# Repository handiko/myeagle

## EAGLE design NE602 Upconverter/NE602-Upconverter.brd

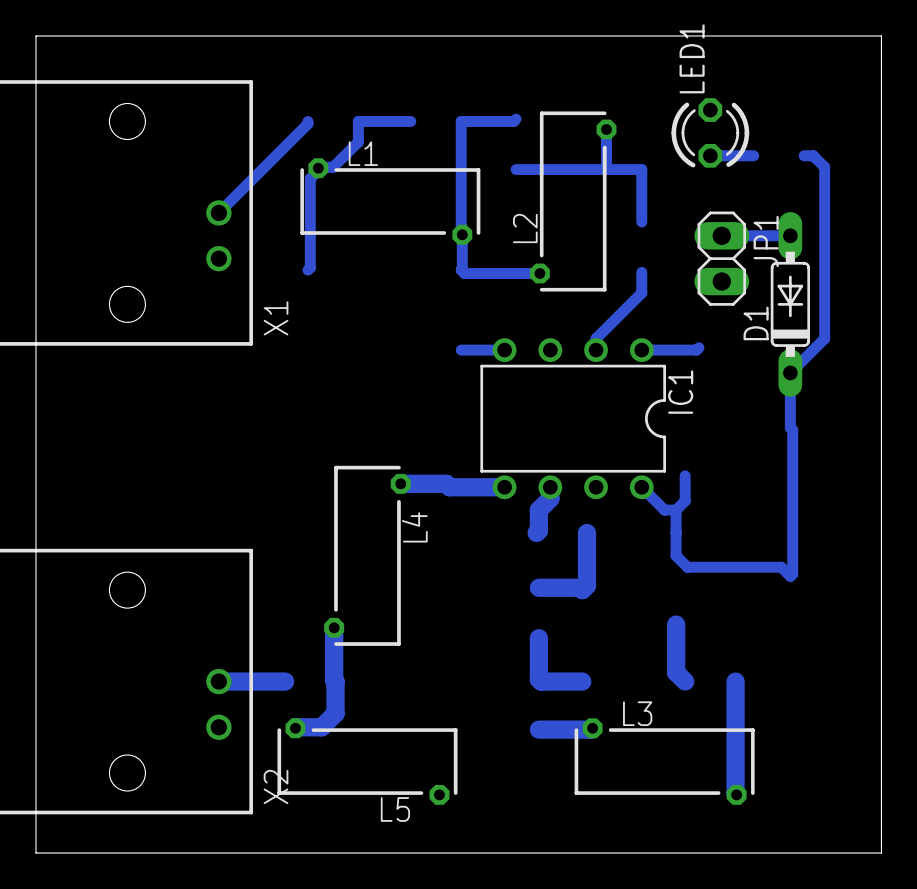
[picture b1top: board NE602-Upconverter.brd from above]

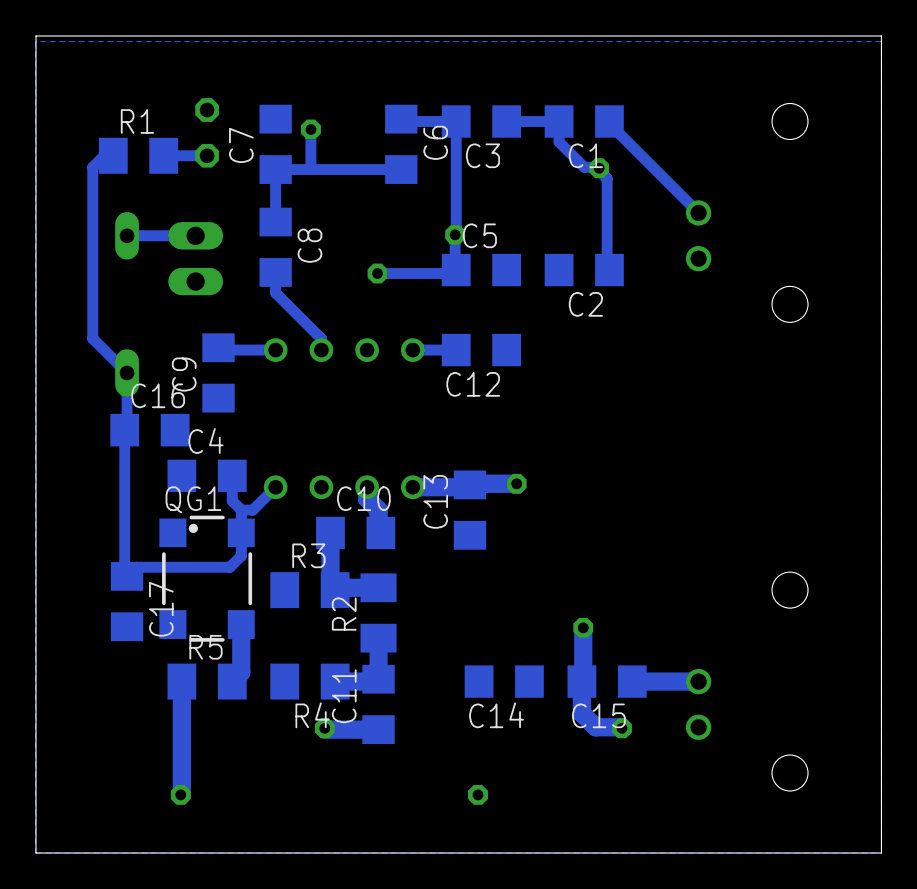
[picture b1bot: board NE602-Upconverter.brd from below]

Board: 2 copper layers, 47.0 x 45.4 mm, 34 parts (23 on the bottom side), 21 nets.

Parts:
C1, C2, C3, C4, C5, C6, C7, C8, C9, C10, C11, C12, C13, C14, C15, C16, C17: C1206
D1: 1N4148DO35-7; DO35-7
IC1: SA612AN; DIL08
JP1: 1X02
L1, L2, L3, L4, L5: Z28/7
LED1: LED3MM
QG1: SM77H
R1, R2, R3, R4, R5: M1206
X1, X2: 1-227161-0; AMP_227161

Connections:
+5V: C4.2, C16.1, C17.1, D1.C, IC1.8, QG1.4, R1.1
GND: C2.2, C4.1, C5.2, C7.2, C9.1, C12.1, C13.1, C14.1, C16.2, C17.2, IC1.3, JP1.2, LED1.K, QG1.2, R3.1, R4.2, X1.2, X2.2
unnamed: C1.2, C2.1, C3.1, L1.2
unnamed: C3.2, C5.1, C6.1, L1.1, L2.2
unnamed: C6.2, C7.1, C8.1, L2.1
unnamed: C8.2, IC1.2
unnamed: C9.2, IC1.1
unnamed: C10.2, IC1.6
unnamed: C14.2, L5.2
unnamed: C13.2, IC1.5, L4.2
unnamed: C15.2, L4.1, L5.1
unnamed: C12.2, IC1.4
unnamed: C11.2, R2.1, R4.1
unnamed: C10.1, R2.2, R3.2
unnamed: C11.1, L3.2
unnamed: LED1.A, R1.2
unnamed: L3.1, R5.1
unnamed: QG1.3, R5.2
unnamed: C1.1, X1.1
unnamed: C15.1, X2.1
unnamed: D1.A, JP1.1

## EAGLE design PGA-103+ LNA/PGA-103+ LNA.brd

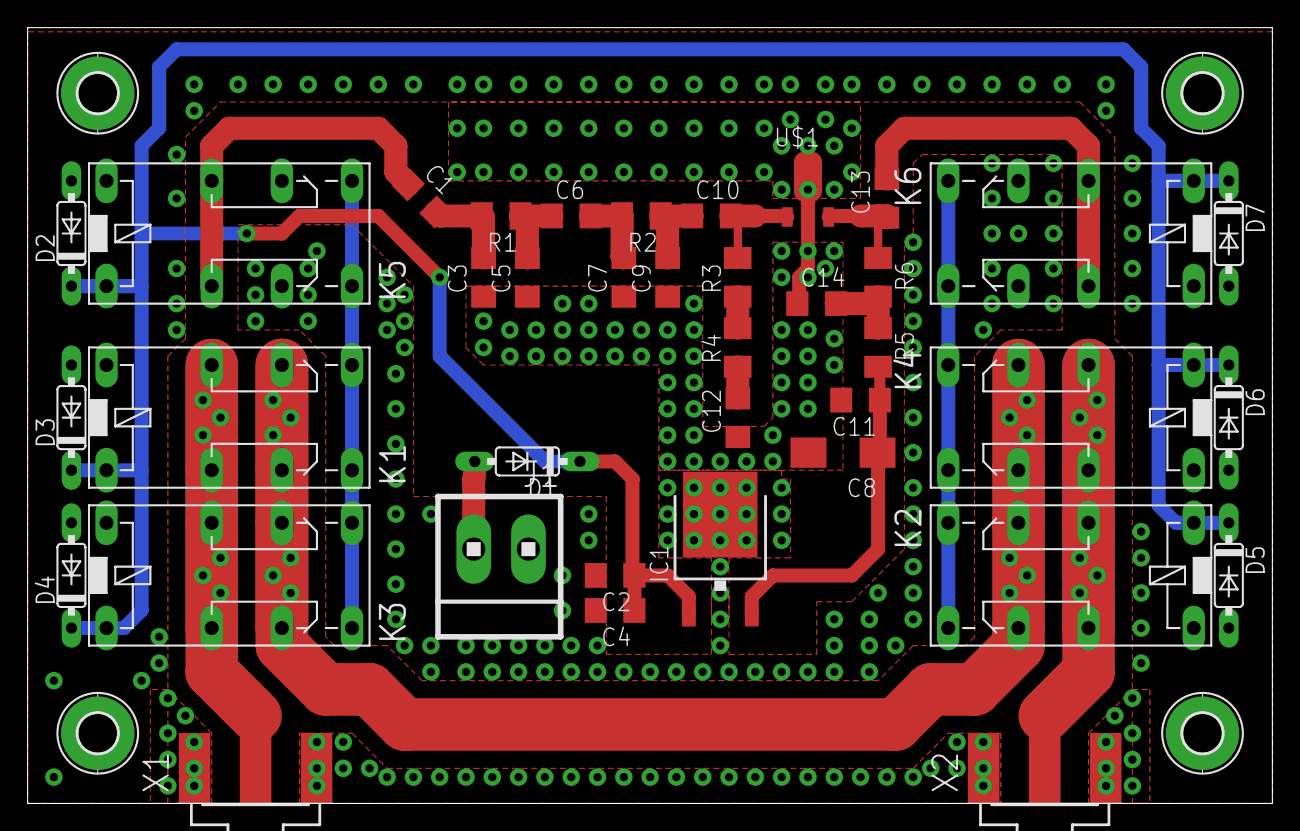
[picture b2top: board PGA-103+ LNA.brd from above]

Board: 2 copper layers, 90.2 x 56.2 mm, 42 parts (0 on the bottom side), 20 nets.

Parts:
C1, C6, C10, C13: 10n; C1206
C2, C4, C11, C14: 1n; C1206
C3, C5, C7, C9, C12: 330p; C1206
C8: 10u; CT6032
D1, D2, D3, D4, D5, D6, D7: 1N4xxx; DO35-7
H1, H2, H3, H4: MOUNT-PAD; 2,8-PAD
IC1: 7805DT; TO252
J1: 1X2MTA
K1, K2, K3, K4, K5, K6: 351
R1, R2, R3, R6: 1u; M1206
R4: 150; M1206
R5: 22; M1206
U$1: PGA-103; DF782
X1, X2: SMA; J502-ND-142-0701-851/861

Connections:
ANT: K1.P1, K1.P2, K3.P1, K3.P2, X1.1
GND: C2.2, C3.1, C4.2, C5.1, C7.1, C8.-, C9.1, C11.2, C12.1, C14.1, D2.A, D3.A, D4.A, D5.A, D6.A, D7.A, H1.B2,8, H2.B2,8, H3.B2,8, H4.B2,8, IC1.3, J1.2, K1.16, K2.16, K3.16, K4.16, K5.16, K5.O1, K5.O2, K6.16, K6.O1, K6.O2, U$1.GND-1, U$1.GND-2, X1.G@1, X1.G@2, X1.G@3, X1.G@4, X2.G@1, X2.G@2, X2.G@3, X2.G@4
LNA_IN: C1.1, K5.P1, K5.P2
LNA_OUT: C13.2, K6.P1, K6.P2
unnamed: C10.2, R3.2, U$1.RF-IN
unnamed: C13.1, R6.1, U$1.RF-OUT
unnamed: C8.+, C11.1, IC1.2, R5.2
unnamed: D1.A, J1.1
unnamed: C9.2, C10.1, R2.1
unnamed: C14.2, R5.1, R6.2
unnamed: R3.1, R4.2
unnamed: C12.2, R4.1
unnamed: C6.2, C7.2, R2.2
unnamed: C5.2, C6.1, R1.1
unnamed: C1.2, C3.2, R1.2
unnamed: K1.S1, K1.S2, K3.S1, K3.S2, K5.S1, K5.S2
unnamed: K2.S1, K2.S2, K4.S1, K4.S2, K6.S1, K6.S2
RF_BYPASS: K1.O1, K1.O2, K2.O1, K2.O2, K3.O1, K3.O2, K4.O1, K4.O2
TRX: K2.P1, K2.P2, K4.P1, K4.P2, X2.1
VCC: C2.1, C4.1, D1.C, D2.C, D3.C, D4.C, D5.C, D6.C, D7.C, IC1.1, K1.1, K2.1, K3.1, K4.1, K5.1, K6.1

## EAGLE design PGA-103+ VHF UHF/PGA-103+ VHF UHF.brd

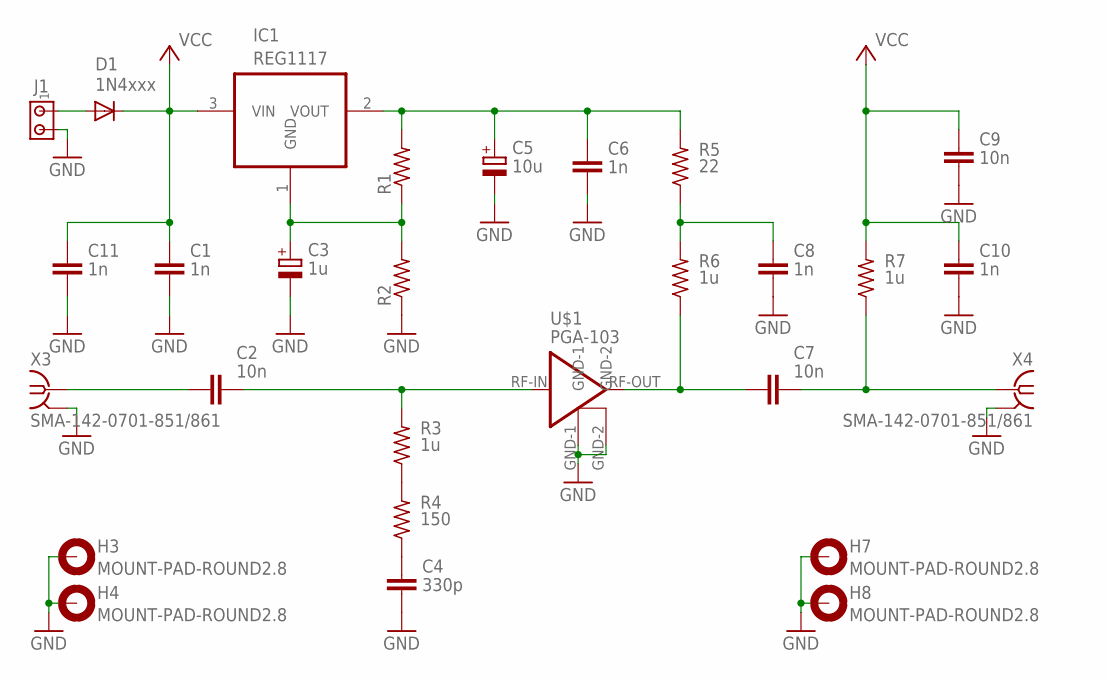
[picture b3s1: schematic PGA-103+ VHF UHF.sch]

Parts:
C1, C6, C8, C10, C11: 1n; C1206
C2, C7, C9: 10n; C1206
C3: 1u; CT6032
C4: 330p; C1206
C5: 10u; CT6032
D1: 1N4xxx; DO35-7
H3, H4, H7, H8: MOUNT-PAD-ROUND2.8; 2,8-PAD
IC1: REG1117; SOT223
J1: MTA02-156; 1X2MTA
R1, R2: R-US_M1206; M1206
R3, R6, R7: 1u; M1206
R4: 150; M1206
R5: 22; M1206
U$1: PGA-103; DF782
X3, X4: SMA-142-0701-851/861; J502-ND-142-0701-851/861

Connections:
GND: C1.2, C3.-, C4.1, C5.-, C6.2, C8.1, C9.1, C10.1, C11.2, H3.B2,8, H4.B2,8, H7.B2,8, H8.B2,8, J1.2, R2.1, U$1.GND-1, U$1.GND-2, X3.G@1 (2), X3.G@2 (2), X3.G@3 (2), X3.G@4 (2), X4.G@1 (2), X4.G@2 (2), X4.G@3 (2), X4.G@4 (2)
unnamed: C2.2, R3.2, U$1.RF-IN
unnamed: C2.1, X3.1
unnamed: C7.1, R6.1, U$1.RF-OUT
unnamed: C7.2, R7.1, X4.1
unnamed: C5.+, C6.1, IC1.2 (VOUT), R1.2, R5.2
unnamed: C3.+, IC1.1 (GND), R1.1, R2.2
unnamed: D1.A, J1.1
unnamed: C8.2, R5.1, R6.2
unnamed: R3.1, R4.2
unnamed: C4.2, R4.1
VCC: C1.1, C9.2, C10.2, C11.1, D1.C, IC1.3 (VIN), R7.2

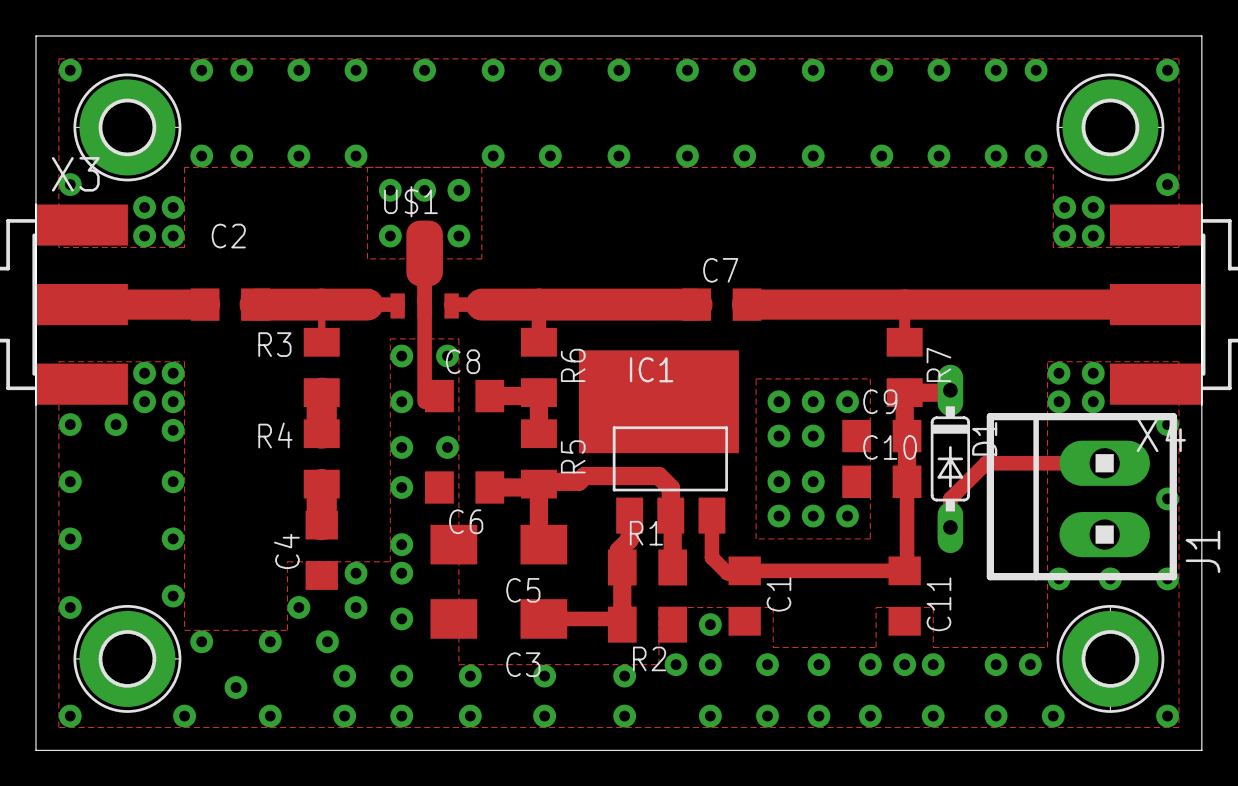
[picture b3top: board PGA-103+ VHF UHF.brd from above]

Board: 2 copper layers, 64.8 x 39.7 mm, 28 parts (0 on the bottom side), 12 nets.

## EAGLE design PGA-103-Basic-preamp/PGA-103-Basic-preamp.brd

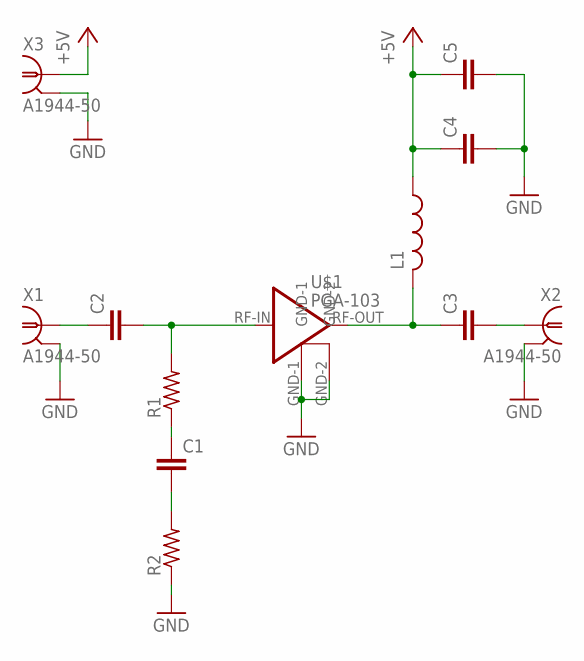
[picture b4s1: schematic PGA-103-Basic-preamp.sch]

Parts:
C1, C2, C3, C4, C5: C-EUC1206; C1206
L1: L-US0204/7; 0204/7
R1, R2: R-US_M1206; M1206
U$1: PGA-103; DF782
X1, X2, X3: A1944-50; A1944

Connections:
+5V: C4.1, C5.1, L1.1, X3.1
GND: C4.2, C5.2, R2.1, U$1.GND-1, U$1.GND-2, X1.2, X1.3 (2), X1.4 (2), X1.5 (2), X2.2, X2.3 (2), X2.4 (2), X2.5 (2), X3.2, X3.3 (2), X3.4 (2), X3.5 (2)
unnamed: C2.1, X1.1
unnamed: C3.1, L1.2, U$1.RF-OUT
unnamed: C2.2, R1.2, U$1.RF-IN
unnamed: C1.1, R1.1
unnamed: C1.2, R2.2
unnamed: C3.2, X2.1

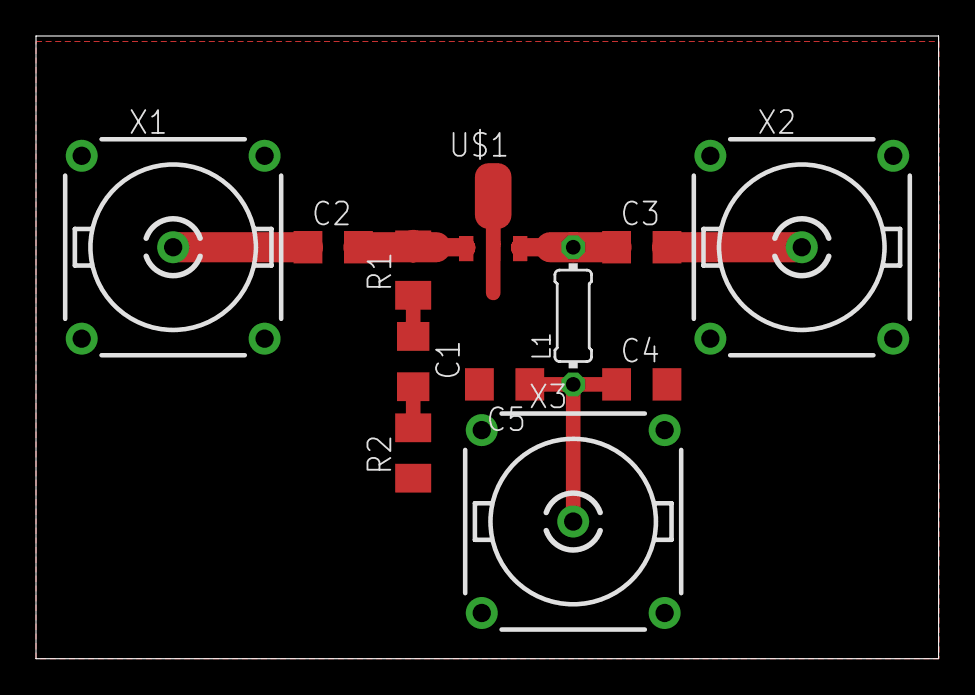
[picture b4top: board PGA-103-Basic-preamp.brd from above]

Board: 2 copper layers, 50.1 x 34.6 mm, 12 parts (0 on the bottom side), 8 nets.

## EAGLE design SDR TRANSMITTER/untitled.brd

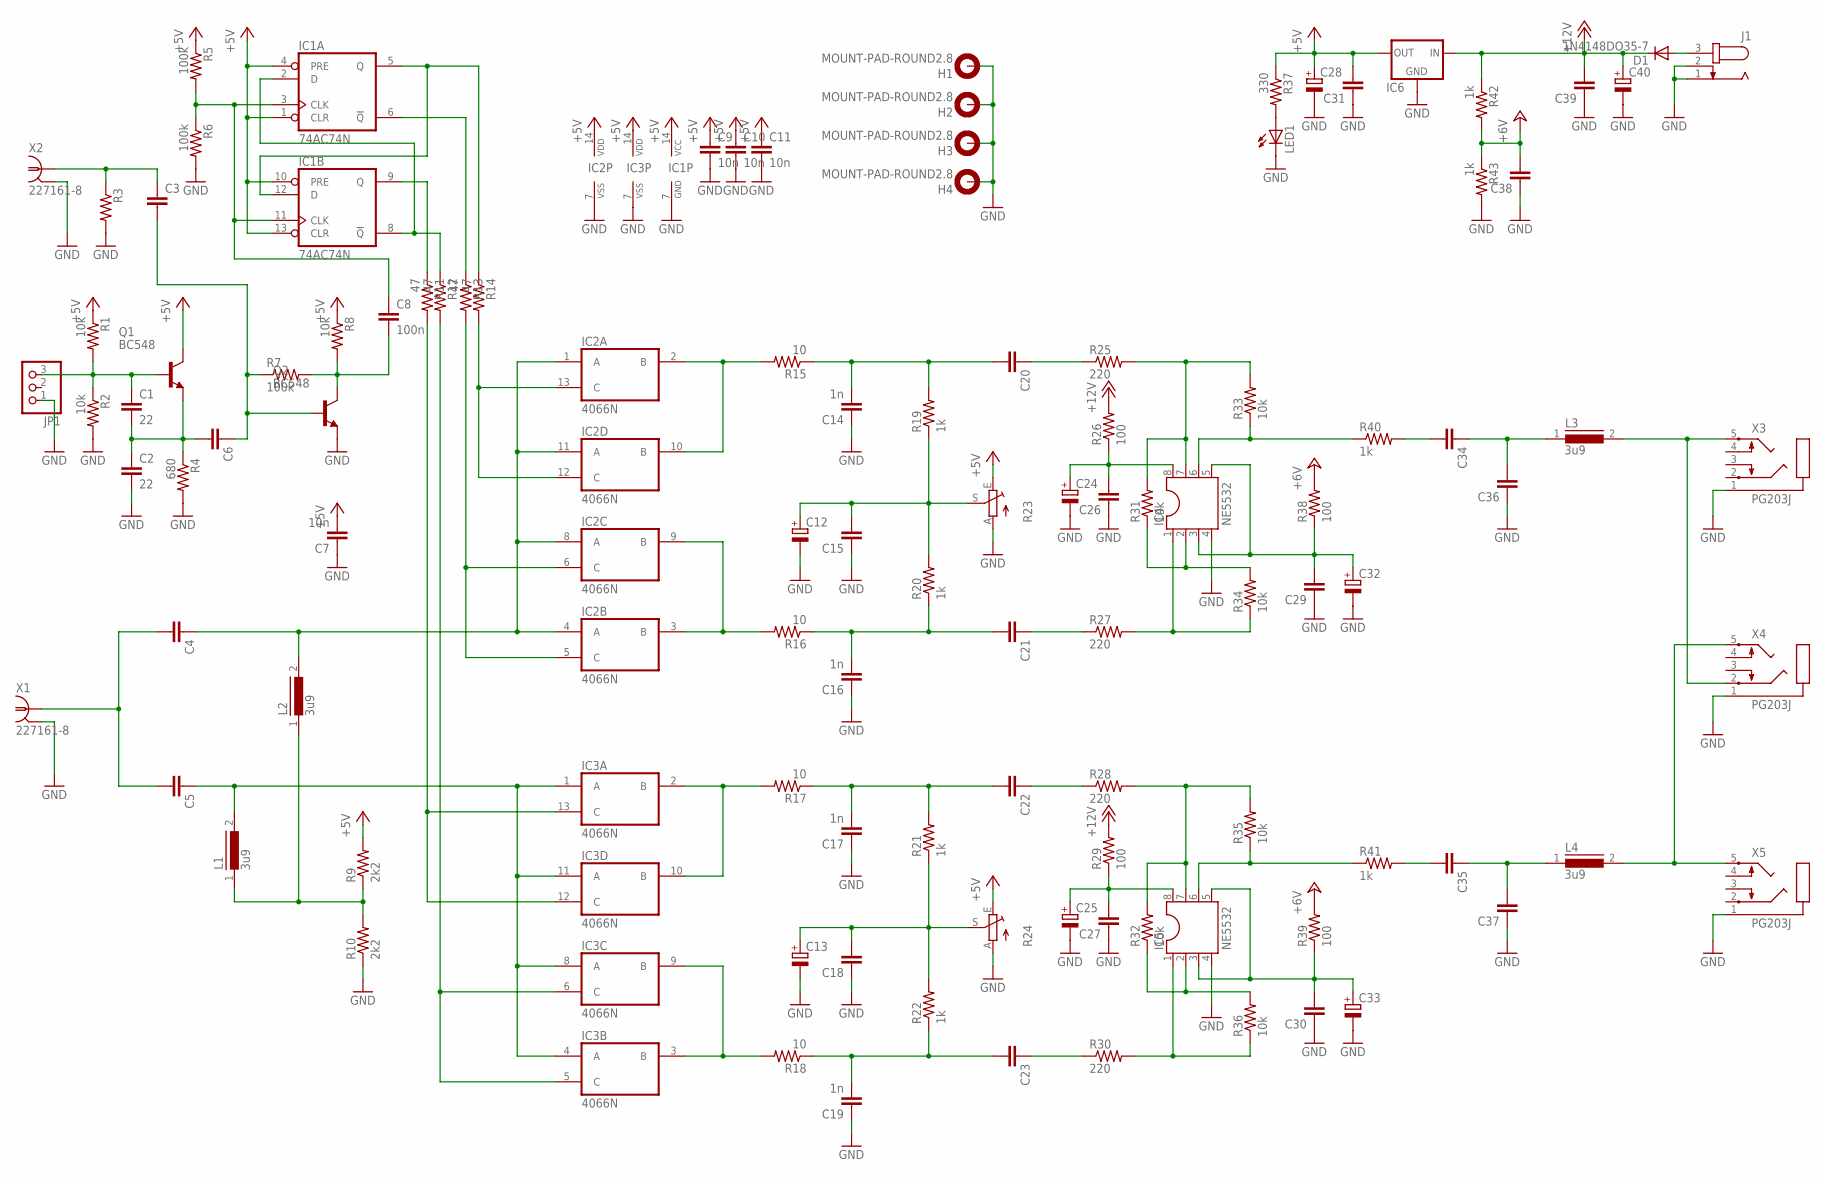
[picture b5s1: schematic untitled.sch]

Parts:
C1, C2: 22; C025-025X050
C3, C4, C5, C6, C15, C18, C20, C21, C22, C23, C26, C27, C29, C30, C31, C34, C35, C36, C37, C38, C39: C-EU050-025X075; C050-025X075
C7, C9, C10, C11: 10n; C050-025X075
C8: 100n; C075-032X103
C12, C13, C24, C25, C28, C32, C33, C40: CPOL-EUE5-6; E5-6
C14, C16, C17, C19: 1n; C050-025X075
D1: 1N4148DO35-7; DO35-7
H1, H2, H3, H4: MOUNT-PAD-ROUND2.8; 2,8-PAD
IC1: 74AC74N; DIL14
IC2, IC3: 4066N; DIL14
IC4, IC5: NE5532; DIL08
IC6: 78XXS
J1: JACK-PLUG0; SPC4077
JP1: PINHD-1X3; 1X03
L1, L2, L3, L4: 3u9; MMICC7
LED1: LED3MM
Q1, Q2: BC548; TO92-EBC
R1, R2, R8, R31, R32, R33, R34, R35, R36: 10k; 0207/7
R3: R-US_0207/7; 0207/7
R4: 680; 0207/7
R5, R6, R7: 100k; 0207/7
R9, R10: 2k2; 0207/7
R11, R12, R13, R14: 47; 0207/7
R15, R16, R17, R18: 10; 0207/7
R19, R20, R21, R22, R40, R41, R42, R43: 1k; 0207/7
R23, R24: TRIM_EU-B64Y; B64Y
R25, R27, R28, R30: 220; 0207/7
R26, R29, R38, R39: 100; 0207/7
R37: 330; 0207/7
X1, X2: 227161-8; AMP_227161
X3, X4, X5: PG203J

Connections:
+5V: C7.2, C9.1, C10.1, C11.1, C28.+, C31.2, IC1.1 (CLR), IC1.4 (PRE), IC1.10 (PRE), IC1.13 (CLR), IC1.14 (VCC), IC2.14 (VDD), IC3.14 (VDD), IC6.OUT, Q1.C, R1.1, R5.1, R8.1, R9.2, R23.E, R24.E, R37.1
+12V: C39.2, C40.+, D1.C, IC6.IN, R26.2, R29.2, R42.1
+24V: C38.2, R38.2, R39.2, R42.2, R43.1
GND: C2.2, C7.1, C9.2, C10.2, C11.2, C12.-, C13.-, C14.1, C15.1, C16.1, C17.1, C18.1, C19.1, C24.-, C25.-, C26.1, C27.1, C28.-, C29.1, C30.1, C31.1, C32.-, C33.-, C36.1, C37.1, C38.1, C39.1, C40.-, H1.B2,8, H2.B2,8, H3.B2,8, H4.B2,8, IC1.7 (GND), IC2.7 (VSS), IC3.7 (VSS), IC4.4, IC5.4, IC6.GND, J1.1, J1.2, JP1.1, LED1.K (C), Q2.E, R2.2, R3.2, R4.2, R6.2, R10.1, R23.A, R24.A, R43.2, X1.2, X2.2, X3.1, X4.1, X5.1
unnamed: L1.1, L2.1, R9.1, R10.2
unnamed: C4.2, C5.2, X1.1
unnamed: C4.1, IC2.1 (A), IC2.4 (A), IC2.8 (A), IC2.11 (A), L2.2
unnamed: C5.1, IC3.1 (A), IC3.4 (A), IC3.8 (A), IC3.11 (A), L1.2
unnamed: IC2.3 (B), IC2.9 (B), R16.2
unnamed: IC2.2 (B), IC2.10 (B), R15.2
unnamed: IC3.2 (B), IC3.10 (B), R17.2
unnamed: IC3.3 (B), IC3.9 (B), R18.2
unnamed: IC2.12 (C), IC2.13 (C), R14.2
unnamed: IC2.5 (C), IC2.6 (C), R13.2
unnamed: IC3.12 (C), IC3.13 (C), R11.2
unnamed: IC3.5 (C), IC3.6 (C), R12.2
unnamed: C14.2, C20.2, R15.1, R19.2
unnamed: C16.2, C21.2, R16.1, R20.1
unnamed: C17.2, C22.2, R17.1, R21.2
unnamed: C19.2, C23.2, R18.1, R22.1
unnamed: IC1.2 (D), IC1.8 (!Q), R12.1
unnamed: IC1.6 (!Q), R13.1
unnamed: IC1.5 (Q), IC1.12 (D), R14.1
unnamed: IC1.9 (Q), R11.1
unnamed: C8.1, IC1.3 (CLK), IC1.11 (CLK), R5.2, R6.1
unnamed: IC4.1, R27.2, R34.1
unnamed: C21.1, R27.1
unnamed: C20.1, R25.1
unnamed: IC4.7, R25.2, R31.2, R33.2
unnamed: IC4.2, R31.1, R34.2
unnamed: IC4.6, R33.1, R40.1
unnamed: C24.+, C26.2, IC4.8, R26.1
unnamed: C29.2, C32.+, IC4.3, IC4.5, R38.1
unnamed: C34.2, R40.2
unnamed: C34.1, C36.2, L3.1
unnamed: C12.+, C15.2, R19.1, R20.2, R23.S
unnamed: D1.A, J1.3
unnamed: C3.1, R3.1, X2.1
unnamed: IC5.1, R30.2, R36.1
unnamed: C23.1, R30.1
unnamed: C22.1, R28.1
unnamed: IC5.7, R28.2, R32.2, R35.2
unnamed: IC5.2, R32.1, R36.2
unnamed: IC5.6, R35.1, R41.1
unnamed: C25.+, C27.2, IC5.8, R29.1
unnamed: C35.2, R41.2
unnamed: C30.2, C33.+, IC5.3, IC5.5, R39.1
unnamed: C35.1, C37.2, L4.1
unnamed: C13.+, C18.2, R21.1, R22.2, R24.S
unnamed: C1.1, JP1.3, Q1.B, R1.2, R2.1
unnamed: C1.2, C2.1, C6.2, Q1.E, R4.1
unnamed: L3.2, X3.5, X4.2
unnamed: C8.2, Q2.C, R7.2, R8.2
unnamed: C3.2, C6.1, Q2.B, R7.1
unnamed: LED1.A, R37.2
unnamed: L4.2, X4.5, X5.5

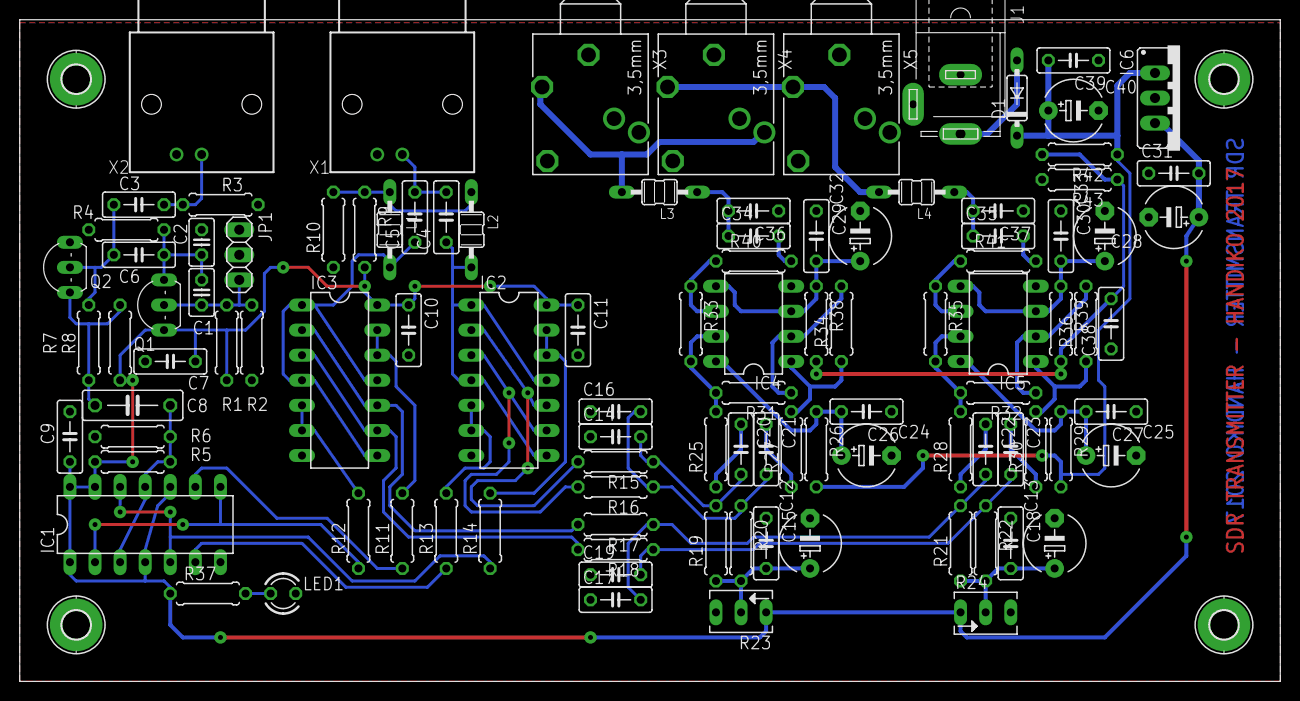
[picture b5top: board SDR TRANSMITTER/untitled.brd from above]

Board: 2 copper layers, 127.6 x 67.0 mm, 108 parts (0 on the bottom side), 56 nets.

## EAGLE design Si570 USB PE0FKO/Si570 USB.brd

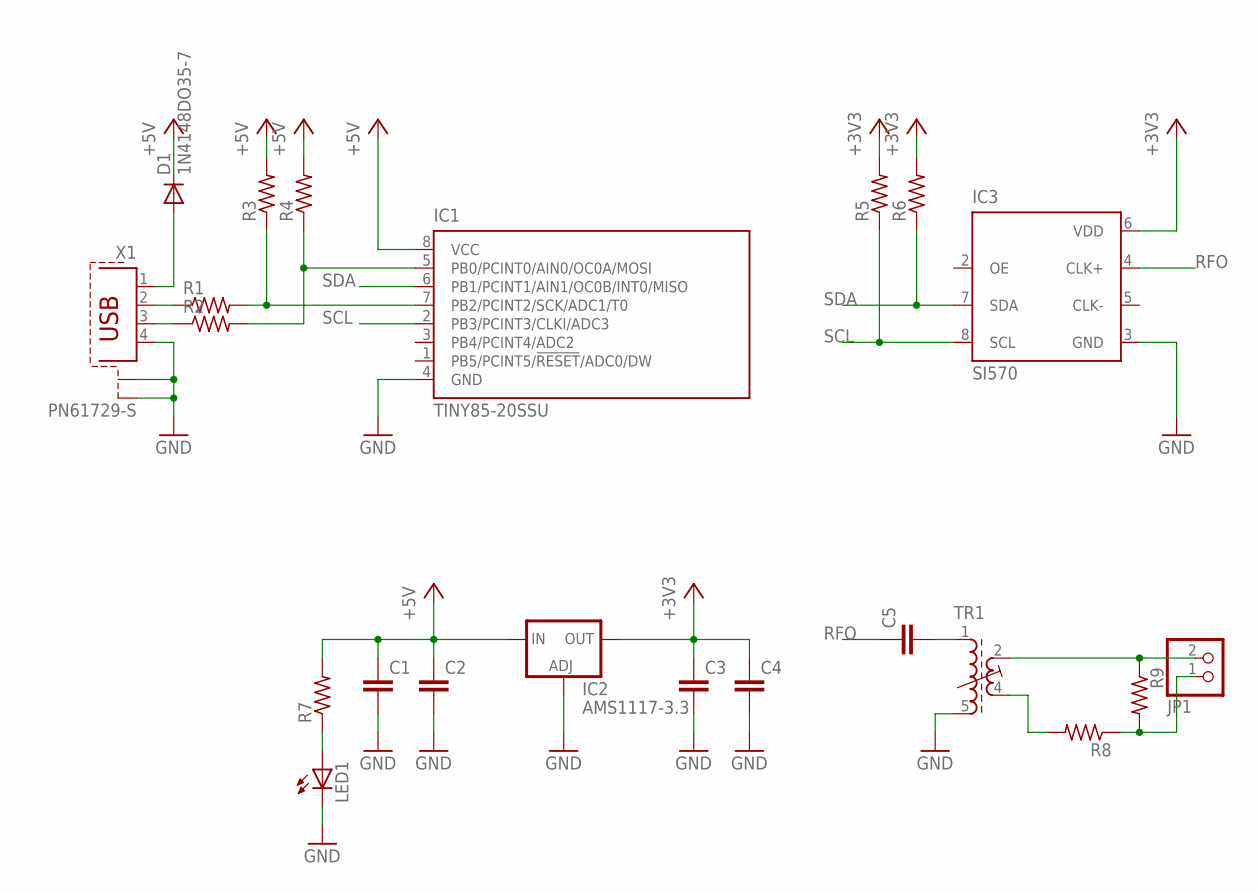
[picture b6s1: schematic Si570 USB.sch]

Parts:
C1, C2, C3, C4, C5: C-EUC1206K; C1206K
D1: 1N4148DO35-7; DO35-7
IC1: TINY85-20SSU; 8S1
IC2: AMS1117-3.3; SOT223
IC3: SI570; 8-PIN
JP1: PINHD-1X2; 1X02
LED1: LED3MM
R1, R2, R3, R4, R5, R6, R7, R8, R9: R-US_R1206; R1206
TR1: 71-4-1542; 71-5
X1: PN61729-S

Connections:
+3V3: C3.1, C4.1, IC2.4 (OUT), IC3.6 (VDD), R5.2, R6.2
+5V: C1.1, C2.1, D1.C, IC1.8 (VCC), IC2.3 (IN), R3.2, R4.2, R7.2
GND: C1.2, C2.2, C3.2, C4.2, IC1.4 (GND), IC2.1 (ADJ), IC3.3 (GND), LED1.K (C), TR1.5 (E1), X1.4, X1.S1, X1.S2
unnamed: R1.1, X1.2
unnamed: R2.1, X1.3
unnamed: D1.A, X1.1
unnamed: IC1.7 (PB2/PCINT2/SCK/ADC1/T0), R1.2, R3.1
unnamed: IC1.5 (PB0/PCINT0/AIN0/OC0A/MOSI), R2.2, R4.1
unnamed: C5.2, TR1.1 (A1)
unnamed: R8.2, TR1.4 (E2)
unnamed: JP1.2, R9.1, TR1.2 (A2)
unnamed: LED1.A, R7.1
unnamed: JP1.1, R8.1, R9.2
RFO: C5.1, IC3.4 (CLK+)
SCL: IC1.2 (PB3/PCINT3/CLKI/ADC3), IC3.8 (SCL), R5.1
SDA: IC1.6 (PB1/PCINT1/AIN1/OC0B/INT0/MISO), IC3.7 (SDA), R6.1

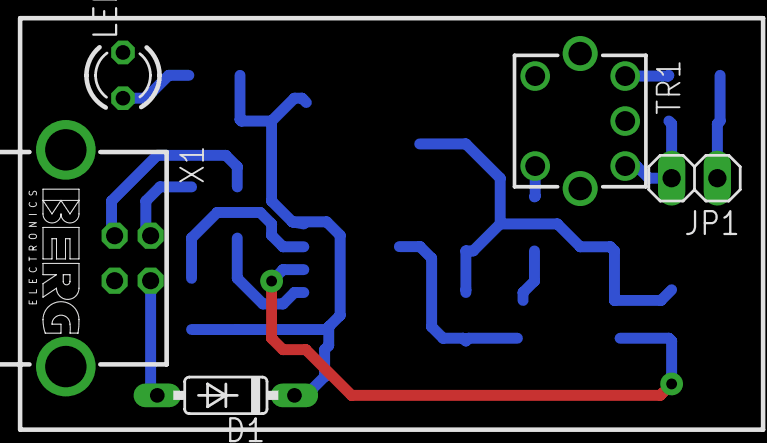
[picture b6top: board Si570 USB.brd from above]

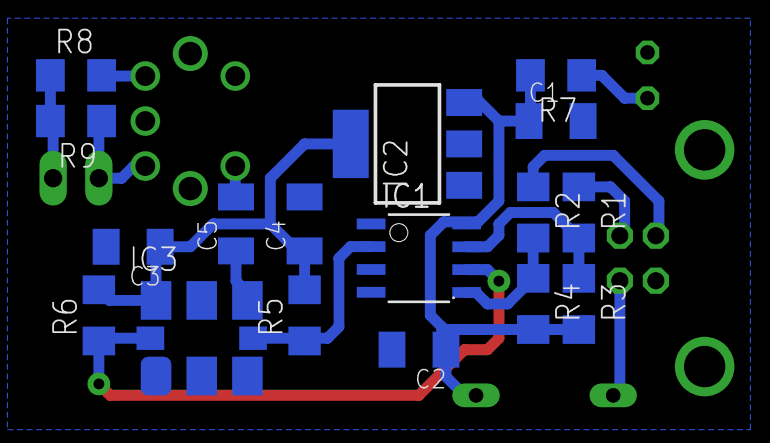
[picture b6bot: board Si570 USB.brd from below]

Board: 2 copper layers, 22 parts (17 on the bottom side), 16 nets.

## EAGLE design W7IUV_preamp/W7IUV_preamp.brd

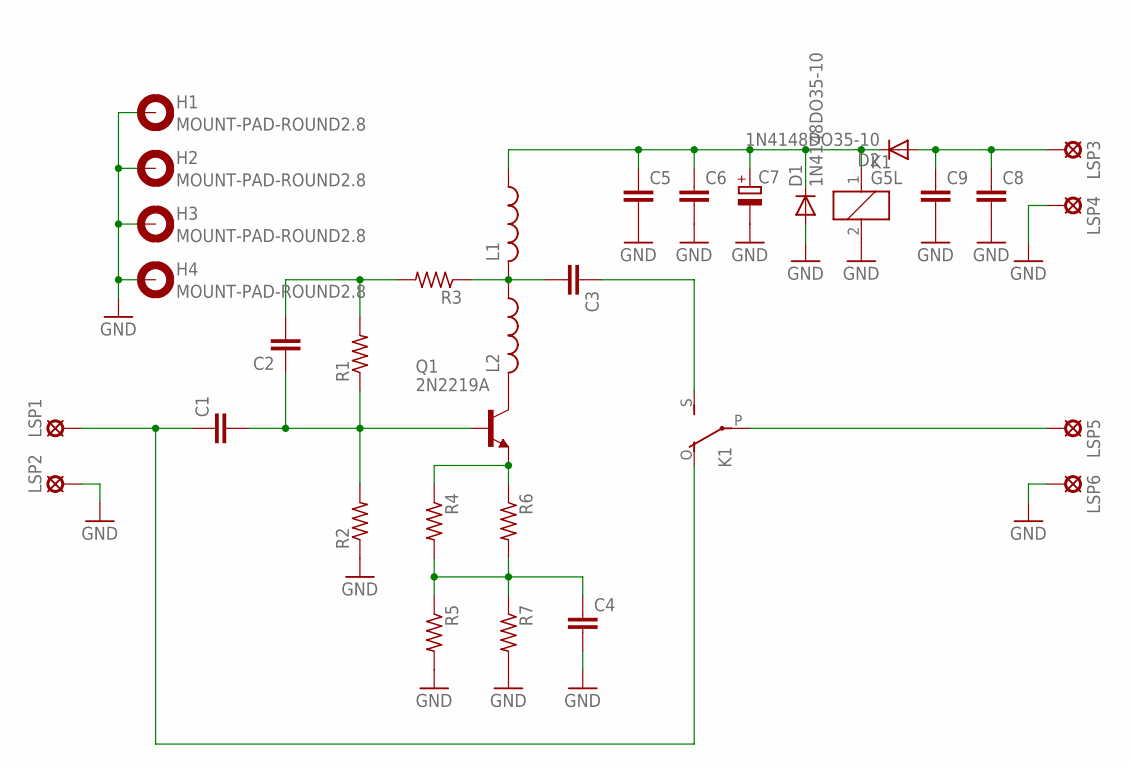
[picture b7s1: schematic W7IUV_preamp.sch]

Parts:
C1, C2, C3, C4, C5, C6, C8, C9: C-EUC1206; C1206
C7: CPOL-EUE5-10.5; E5-10,5
D1, D2: 1N4148DO35-10; DO35-10
H1, H2, H3, H4: MOUNT-PAD-ROUND2.8; 2,8-PAD
K1: G5L; G5LE
L1, L2: L-USLAN02KR; LAN02KR
LSP1, LSP2, LSP3, LSP4, LSP5, LSP6: MCS08
Q1: 2N2219A; TO39
R1, R2, R3, R4, R5, R6, R7: R-US_M1206; M1206

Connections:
GND: C4.2, C5.2, C6.2, C7.-, C8.2, C9.2, D1.A, H1.B2,8, H2.B2,8, H3.B2,8, H4.B2,8, K1.2, LSP2.MP, LSP4.MP, LSP6.MP, R2.1, R5.2, R7.2
unnamed: C4.1, R4.2, R5.1, R6.2, R7.1
unnamed: Q1.1 (E), R4.1, R6.1
unnamed: C1.2, C2.1, Q1.2 (B), R1.1, R2.2
unnamed: C3.1, K1.S
unnamed: C2.2, R1.2, R3.2
unnamed: C3.2, L1.2, L2.1, R3.1
unnamed: L2.2, Q1.3 (C)
unnamed: C1.1, K1.O, LSP1.MP
unnamed: K1.P, LSP5.MP
unnamed: C5.1, C6.1, C7.+, D1.C, D2.C, K1.1, L1.1
unnamed: C8.1, C9.1, D2.A, LSP3.MP

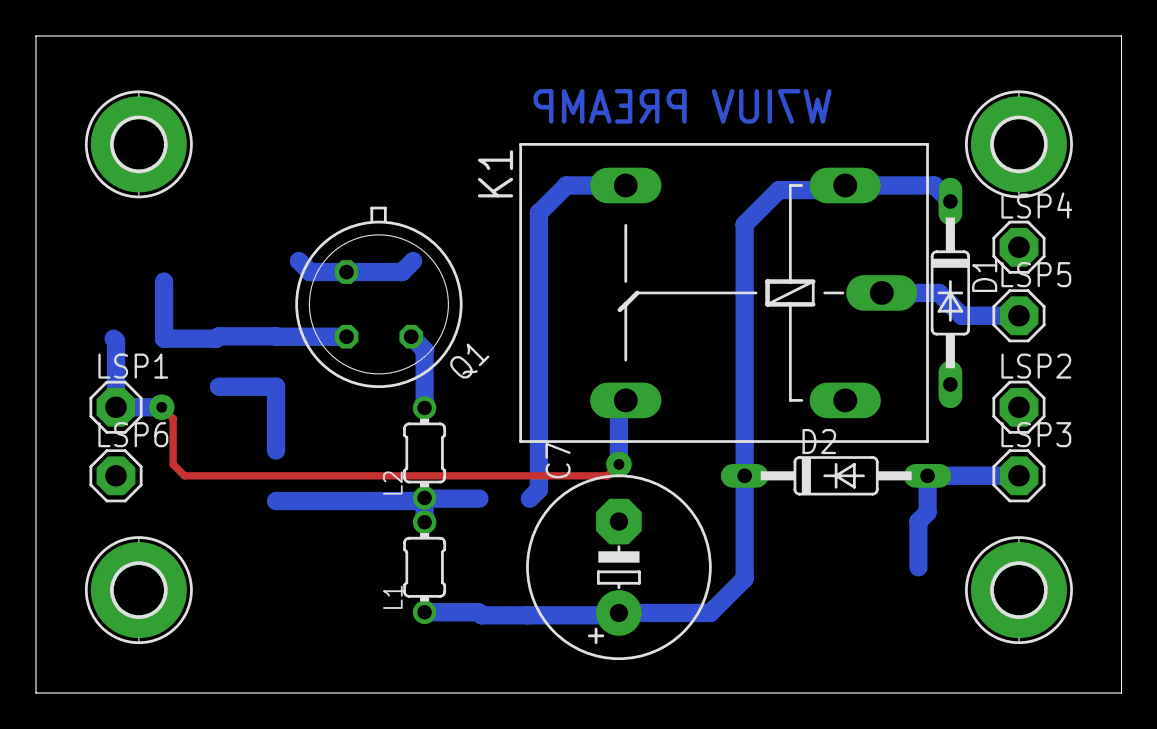
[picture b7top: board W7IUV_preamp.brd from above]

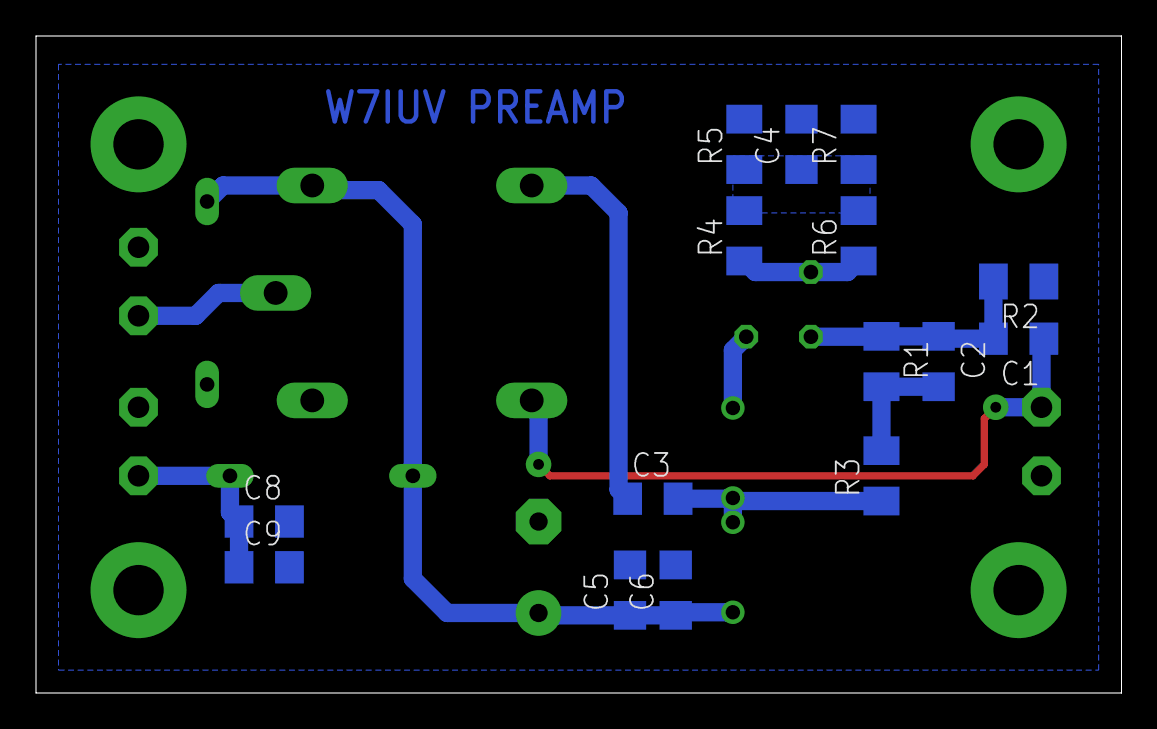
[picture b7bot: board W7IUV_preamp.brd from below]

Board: 2 copper layers, 60.3 x 36.5 mm, 32 parts (15 on the bottom side), 12 nets.

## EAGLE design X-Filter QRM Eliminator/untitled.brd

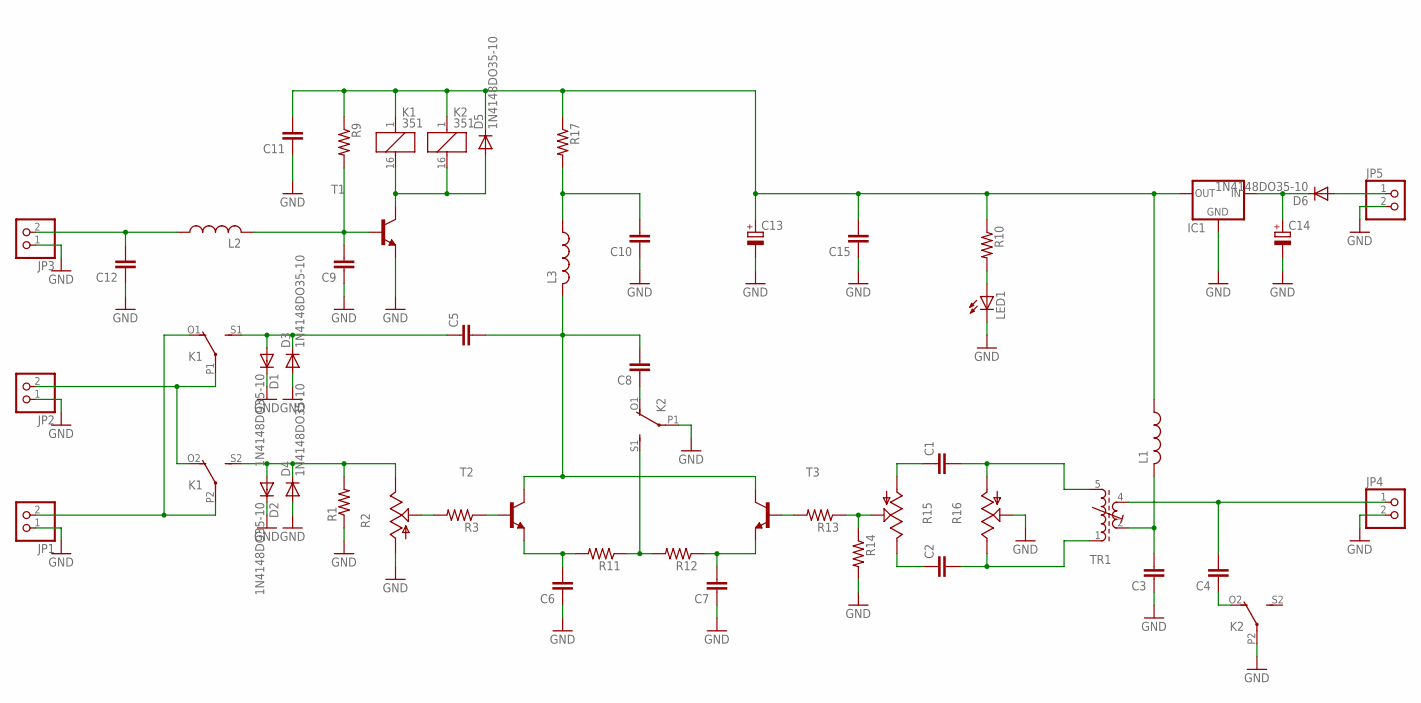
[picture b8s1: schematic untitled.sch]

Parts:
C1, C2, C3, C4, C5, C6, C7, C8, C9, C10, C11, C12, C15: C-EU050-025X075; C050-025X075
C13, C14: CPOL-EUE2.5-5; E2,5-5
D1, D2, D3, D4, D5, D6: 1N4148DO35-10; DO35-10
IC1: 78XXS
JP1, JP2, JP3, JP4, JP5: PINHD-1X2; 1X02
K1, K2: 351
L1, L2, L3: L-US0207/7; 0207/7
LED1: LED3MM
R1: R-US_0309/12; 0309/12
R2, R15, R16: TRIM_US-CIP20C-6MM; CIP20C-6MM
R3, R9, R10, R11, R12, R13, R14, R17: R-US_0207/7; 0207/7
T1, T2, T3: -NPN-TO92-EBC; TO92-EBC
TR1: 71-4-1524; 71-5

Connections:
GND: C3.1, C6.1, C7.1, C9.1, C10.1, C11.1, C12.1, C13.-, C14.-, C15.1, D1.C, D2.C, D3.A, D4.A, IC1.GND, JP1.1, JP2.1, JP3.1, JP4.2, JP5.2, K2.P1, K2.P2, LED1.K (C), R1.1, R2.A, R14.2, R16.S, T1.E
unnamed: JP2.2, K1.O2 (O), K1.P1
unnamed: JP1.2, K1.O1 (O), K1.P2
unnamed: C5.1, D1.A, D3.C, K1.S1 (S)
unnamed: D2.A, D4.C, K1.S2 (S), R1.2, R2.E
unnamed: R2.S, R3.2
unnamed: R3.1, T2.B
unnamed: C6.2, R11.2, T2.E
unnamed: K2.S1 (S), R11.1, R12.2
unnamed: C7.2, R12.1, T3.E
unnamed: R13.1, R14.1, R15.S
unnamed: R13.2, T3.B
unnamed: C1.2, R16.A, TR1.5 (E1)
unnamed: C2.2, R16.E, TR1.1 (A1)
unnamed: C2.1, R15.E
unnamed: C1.1, R15.A
unnamed: C5.2, C8.2, L3.2, T2.C, T3.C
unnamed: LED1.A, R10.2
unnamed: C4.1, K2.O2 (O)
unnamed: C3.2, L1.2, TR1.2 (A2)
unnamed: C4.2, JP4.1, TR1.4 (E2)
unnamed: C12.2, JP3.2, L2.1
unnamed: C8.1, K2.O1 (O)
unnamed: C9.2, L2.2, R9.2, T1.B
unnamed: D5.A, K1.16 (2), K2.16 (2), T1.C
unnamed: C14.+, D6.C, IC1.IN
unnamed: C11.2, C13.+, C15.2, D5.C, IC1.OUT, K1.1, K2.1, L1.1, R9.1, R10.1, R17.1
unnamed: C10.2, L3.1, R17.2
unnamed: D6.A, JP5.1

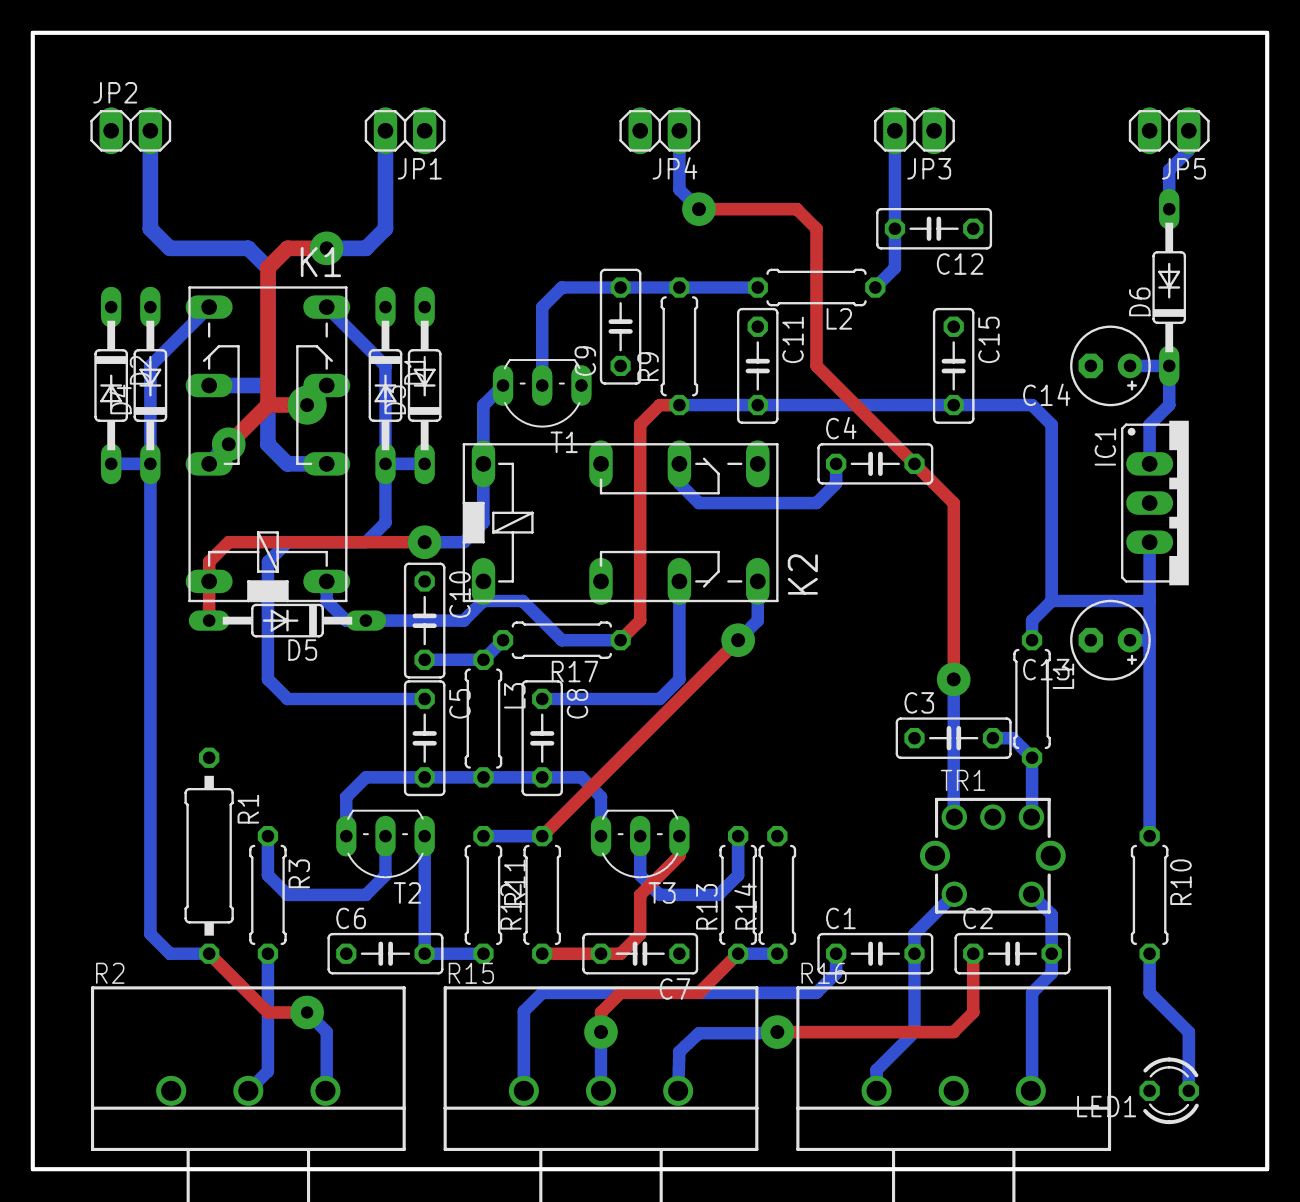
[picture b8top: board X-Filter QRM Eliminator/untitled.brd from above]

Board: 2 copper layers, 80.0 x 73.7 mm, 49 parts (0 on the bottom side), 29 nets.
